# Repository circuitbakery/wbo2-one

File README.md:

# wbo2-one
LSU 4.9 Lambda Oxygen Sensor Interface Repository

##Directories description
* **/Hardware** - Complete board schematic and PCB design in Eagle
* **/Software** - Source code for AVR on board
* **/Documents** - All neccecary documentation

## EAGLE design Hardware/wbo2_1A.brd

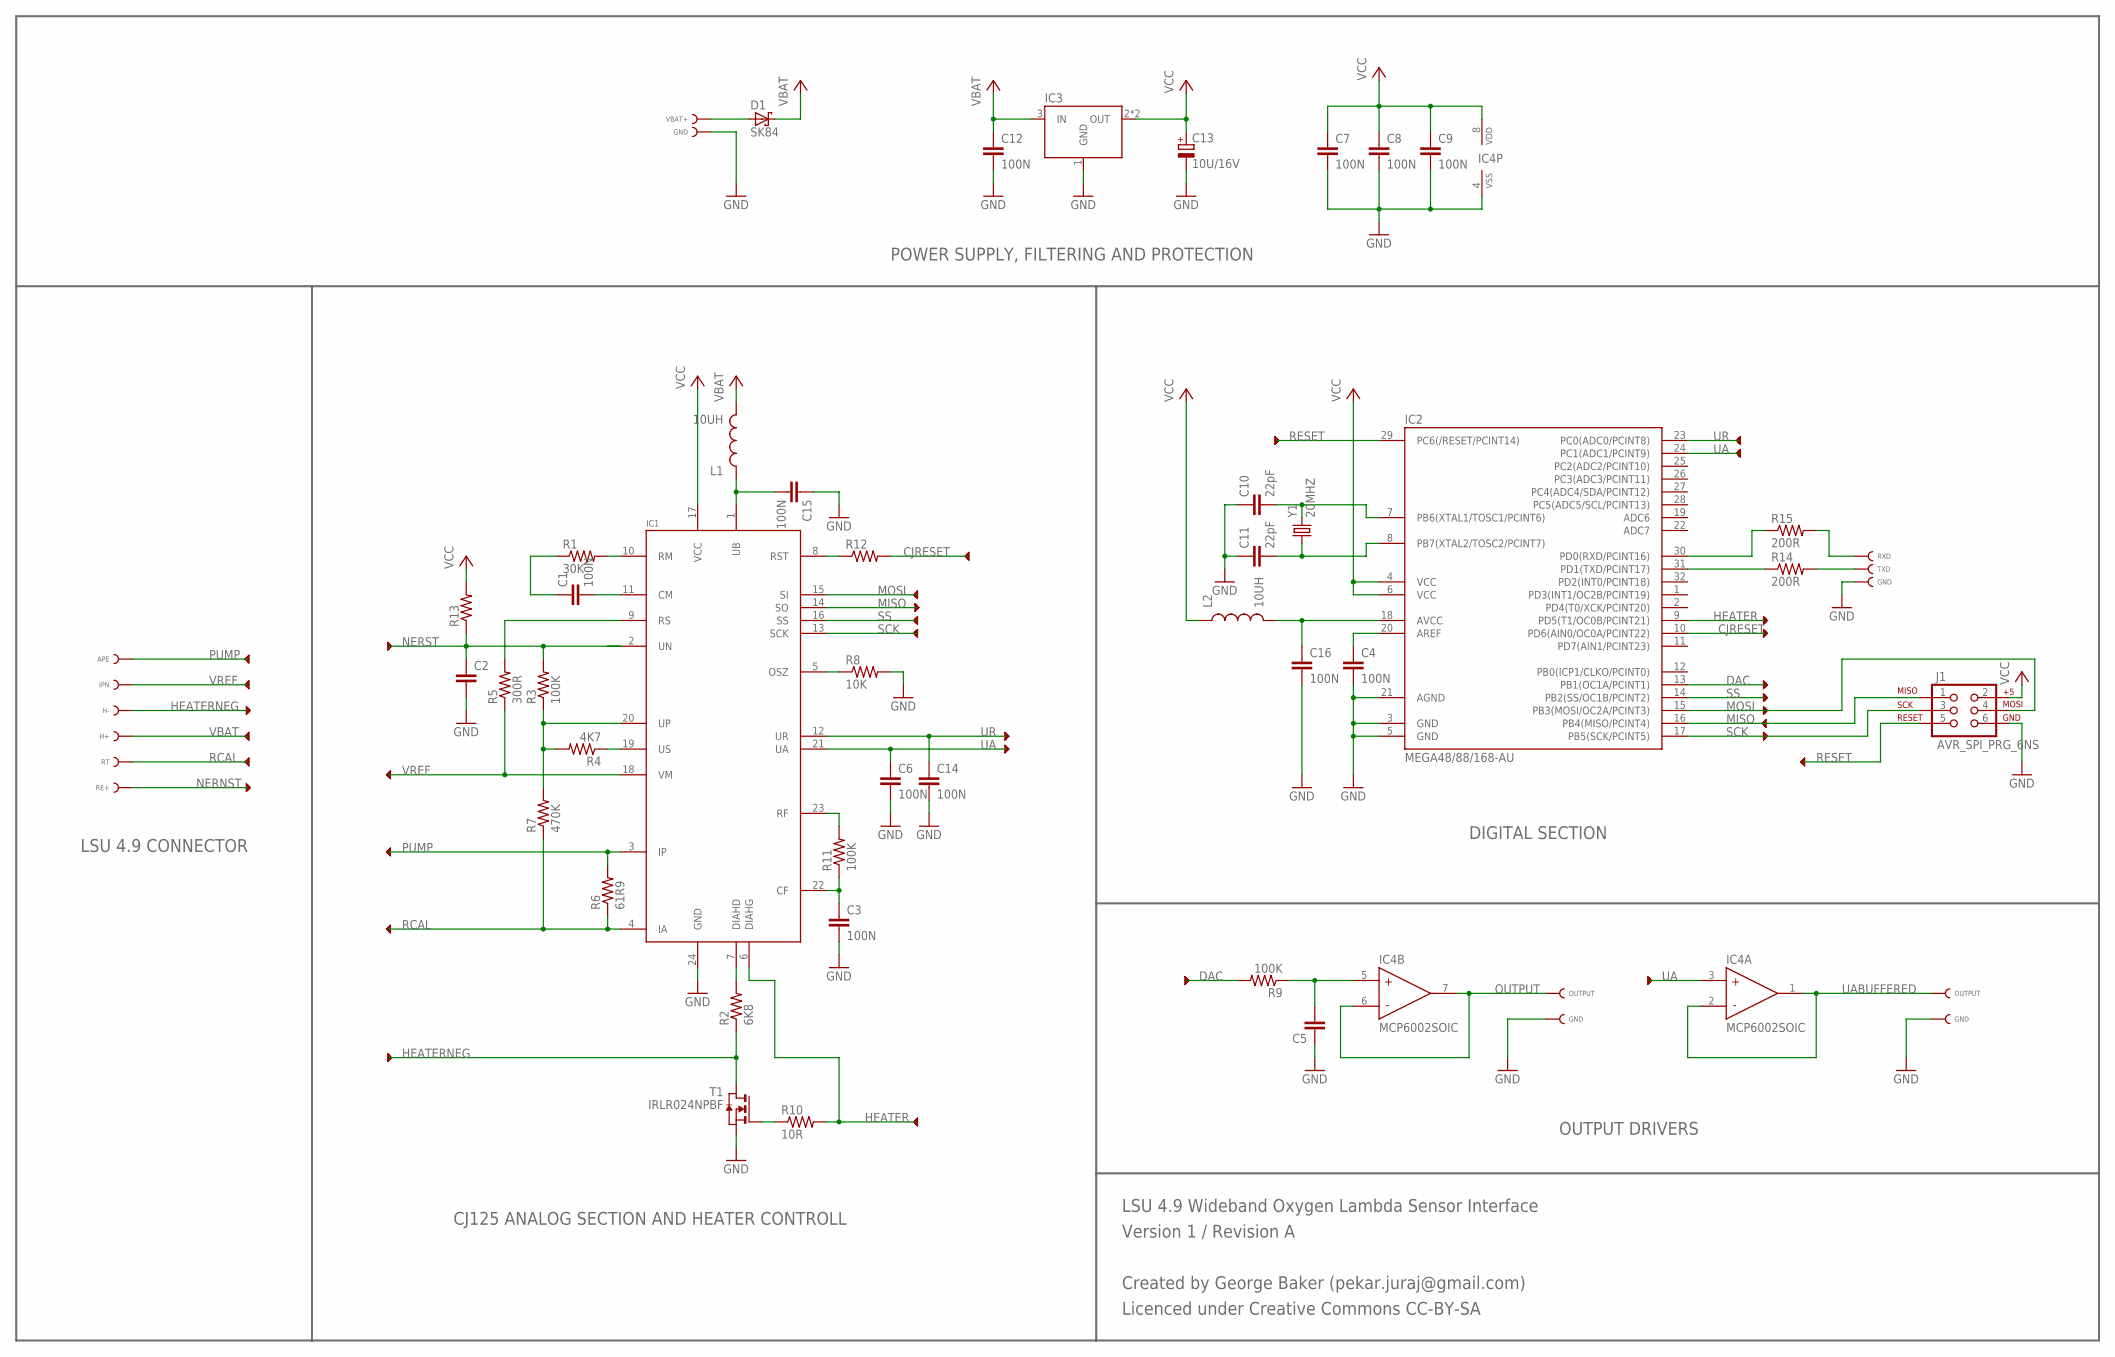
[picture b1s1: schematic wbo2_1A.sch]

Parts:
C1, C3, C4, C6, C7, C8, C9, C12, C14, C15, C16: 100N; 0805
C2, C5: CAP0805; 0805
C10, C11: 22pF; 0805
C13: 10U/16V; SMC_A
D1: SK84; SMC
IC1: CJ125_SOIC24; SO24W
IC2: MEGA48/88/168-AU; TQFP32-08
IC3: REG1117_SOT-223; SOT223
IC4: MCP6002SOIC; SO8
J1: AVR_SPI_PRG_6NS; 2X3-NS
L1, L2: 10UH; 0805
PAD1: APE; CONPAD-DUAL-HOLE-1.5MM
PAD2: IPN; CONPAD-DUAL-HOLE-1.5MM
PAD3: H-; CONPAD-DUAL-HOLE-1.5MM
PAD4: H+; CONPAD-DUAL-HOLE-1.5MM
PAD5: RT; CONPAD-DUAL-HOLE-1.5MM
PAD6: RE+; CONPAD-DUAL-HOLE-1.5MM
PAD7: VBAT+; CONPAD-DUAL-HOLE-1.5MM
PAD8, PAD11, PAD13, PAD15: GND; CONPAD-DUAL-HOLE-1.5MM
PAD9: RXD; CONPAD-DUAL-HOLE-1.5MM
PAD10: TXD; CONPAD-DUAL-HOLE-1.5MM
PAD12, PAD14: OUTPUT; CONPAD-DUAL-HOLE-1.5MM
R1: 30K; 0805
R2: 6K8; 0805
R3, R9, R11: 100K; 0805
R4: 4K7; 0805
R5: 300R; 0805
R6: 61R9; 0805
R7: 470K; 0805
R8: 10K; 0805
R10: 10R; 0805
R12, R13: RESISTOR0805-RES; 0805
R14, R15: 200R; 0805
T1: IRLR024NPBF; TO252
Y1: 20MHZ; CRYSTAL_ILCX13

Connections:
CJRESET: IC2.10 (PD6(AIN0/OC0A/PCINT22)), R12.2
DAC: IC2.13 (PB1(OC1A/PCINT1)), R9.2
GND: C2.2, C3.2, C4.2, C5.1, C6.2, C7.2, C8.2, C9.2, C10.1, C11.1, C12.2, C13.-, C14.2, C15.1, C16.2, IC1.24 (GND), IC2.3 (GND), IC2.5 (GND), IC2.21 (AGND), IC3.1 (GND), IC4.4 (VSS), J1.6, PAD8.P$1@1, PAD8.P$1@2, PAD11.P$1@1, PAD11.P$1@2, PAD13.P$1@1, PAD13.P$1@2, PAD15.P$1@1, PAD15.P$1@2, R8.2, T1.2 (S)
HEATER: IC1.6 (DIAHG), IC2.9 (PD5(T1/OC0B/PCINT21)), R10.2
HEATERNEG: PAD3.P$1@1, PAD3.P$1@2, R2.1, T1.3 (D)
MISO: IC1.14 (SO), IC2.16 (PB4(MISO/PCINT4)), J1.1
MOSI: IC1.15 (SI), IC2.15 (PB3(MOSI/OC2A/PCINT3)), J1.4
unnamed: IC1.7 (DIAHD), R2.2
unnamed: IC1.23 (RF), R11.2
unnamed: C3.1, IC1.22 (CF), R11.1
unnamed: C16.1, IC2.18 (AVCC), L2.2
unnamed: C15.2, IC1.1 (UB), L1.1
unnamed: IC1.19 (US), R4.1
unnamed: C4.1, IC2.20 (AREF)
unnamed: IC1.20 (UP), R3.1, R4.2, R7.2
unnamed: C10.2, IC2.7 (PB6(XTAL1/TOSC1/PCINT6)), Y1.3 (2)
unnamed: C5.2, IC4.5 (NONINV), R9.1
unnamed: C11.2, IC2.8 (PB7(XTAL2/TOSC2/PCINT7)), Y1.1
unnamed: D1.A, PAD7.P$1@1, PAD7.P$1@2
unnamed: IC1.10 (RM), R1.2
unnamed: R10.1, T1.1 (G)
unnamed: PAD10.P$1@1, PAD10.P$1@2, R14.2
unnamed: IC1.9 (RS), R5.2
unnamed: PAD9.P$1@1, PAD9.P$1@2, R15.2
unnamed: C1.1, R1.1
unnamed: C1.2, IC1.11 (CM)
unnamed: IC1.5 (OSZ), R8.1
unnamed: IC1.8 (RST), R12.1
NERNST: PAD6.P$1@1, PAD6.P$1@2
NERST: C2.1, IC1.2 (UN), R3.2, R13.1
OUTPUT: IC4.6 (INV), IC4.7 (OUT), PAD12.P$1@1, PAD12.P$1@2
PUMP: IC1.3 (IP), PAD1.P$1@1, PAD1.P$1@2, R6.2
RCAL: IC1.4 (IA), PAD5.P$1@1, PAD5.P$1@2, R6.1, R7.1
RESET: IC2.29 (PC6(/RESET/PCINT14)), J1.5
RXD: IC2.30 (PD0(RXD/PCINT16)), R15.1
SCK: IC1.13 (SCK), IC2.17 (PB5(SCK/PCINT5)), J1.3
SS: IC1.16 (SS), IC2.14 (PB2(SS/OC1B/PCINT2))
TXD: IC2.31 (PD1(TXD/PCINT17)), R14.1
UA: C6.1, IC1.21 (UA), IC2.24 (PC1(ADC1/PCINT9)), IC4.3 (NONINV)
UABUFFERED: IC4.1 (OUT), IC4.2 (INV), PAD14.P$1@1, PAD14.P$1@2
UR: C14.1, IC1.12 (UR), IC2.23 (PC0(ADC0/PCINT8))
VBAT: C12.1, D1.C, IC3.3 (IN), L1.2, PAD4.P$1@1, PAD4.P$1@2
VCC: C7.1, C8.1, C9.1, C13.+, IC1.17 (VCC), IC2.4 (VCC), IC2.6 (VCC), IC3.2 (OUT), IC3.4 (OUT), IC4.8 (VDD), J1.2, L2.1, R13.2
VREF: IC1.18 (VM), PAD2.P$1@1, PAD2.P$1@2, R5.1

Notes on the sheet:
POWER SUPPLY, FILTERING AND PROTECTION
CJ125 ANALOG SECTION AND HEATER CONTROLL
OUTPUT DRIVERS
DIGITAL SECTION
LSU 4.9 CONNECTOR
LSU 4.9 Wideband Oxygen Lambda Sensor Interface
Created by George Baker (pekar.juraj@gmail.com)
Licenced under Creative Commons CC-BY-SA
Version 1 / Revision A

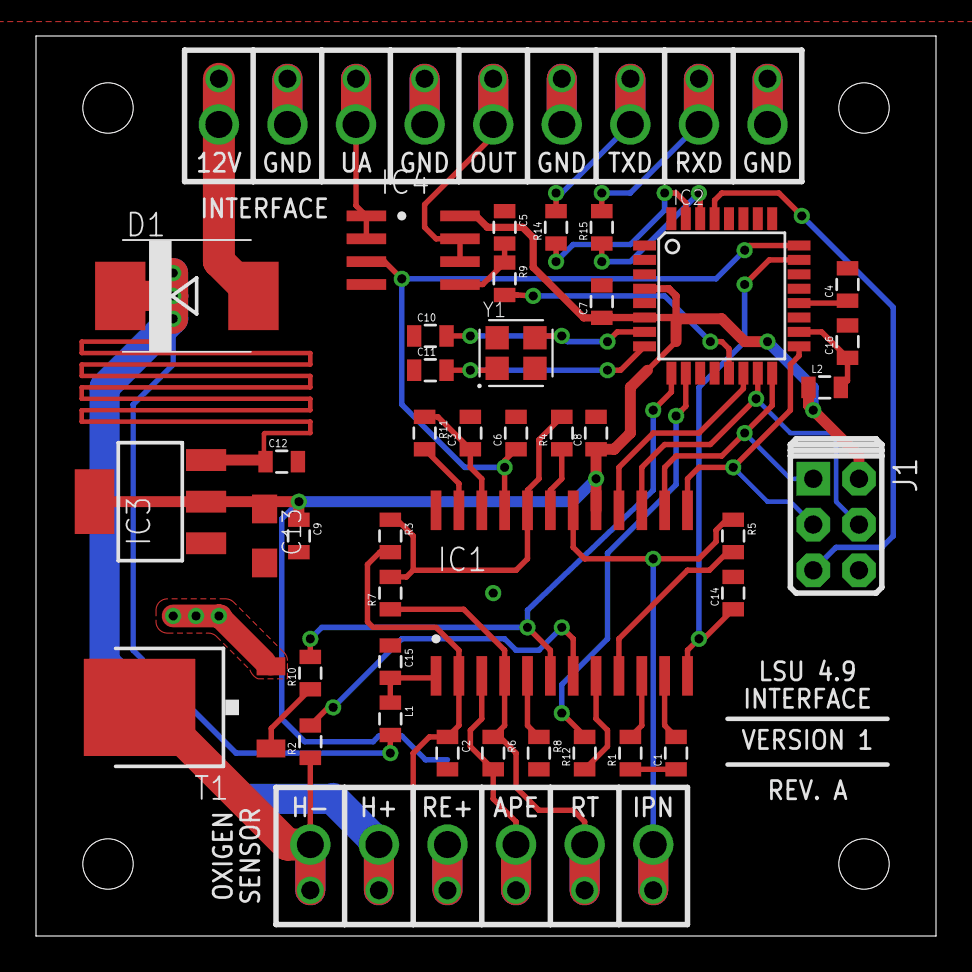
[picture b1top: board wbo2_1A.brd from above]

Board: 2 copper layers, 50.0 x 50.0 mm, 56 parts (1 on the bottom side), 44 nets.

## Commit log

2016-06-30 Update LICENSE
2016-06-30 Add eagle board files with gerbers
2016-06-30 Add CJ125 and LSU 4.9 documentation
2016-07-01 Fixed names
2016-07-01 Upload latest schematic and PCB design

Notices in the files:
parts and their libraries:
SparkFun-Connectors: Licensing: CC v3.0 Share-Alike You are welcome to use this library for commercial purposes.
